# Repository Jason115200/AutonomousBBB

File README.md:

All code is severely outdated. The "REST Board" needs to be updated, but is proof of a great rough draft. For updated code and board, visit REST_Autonomous repository

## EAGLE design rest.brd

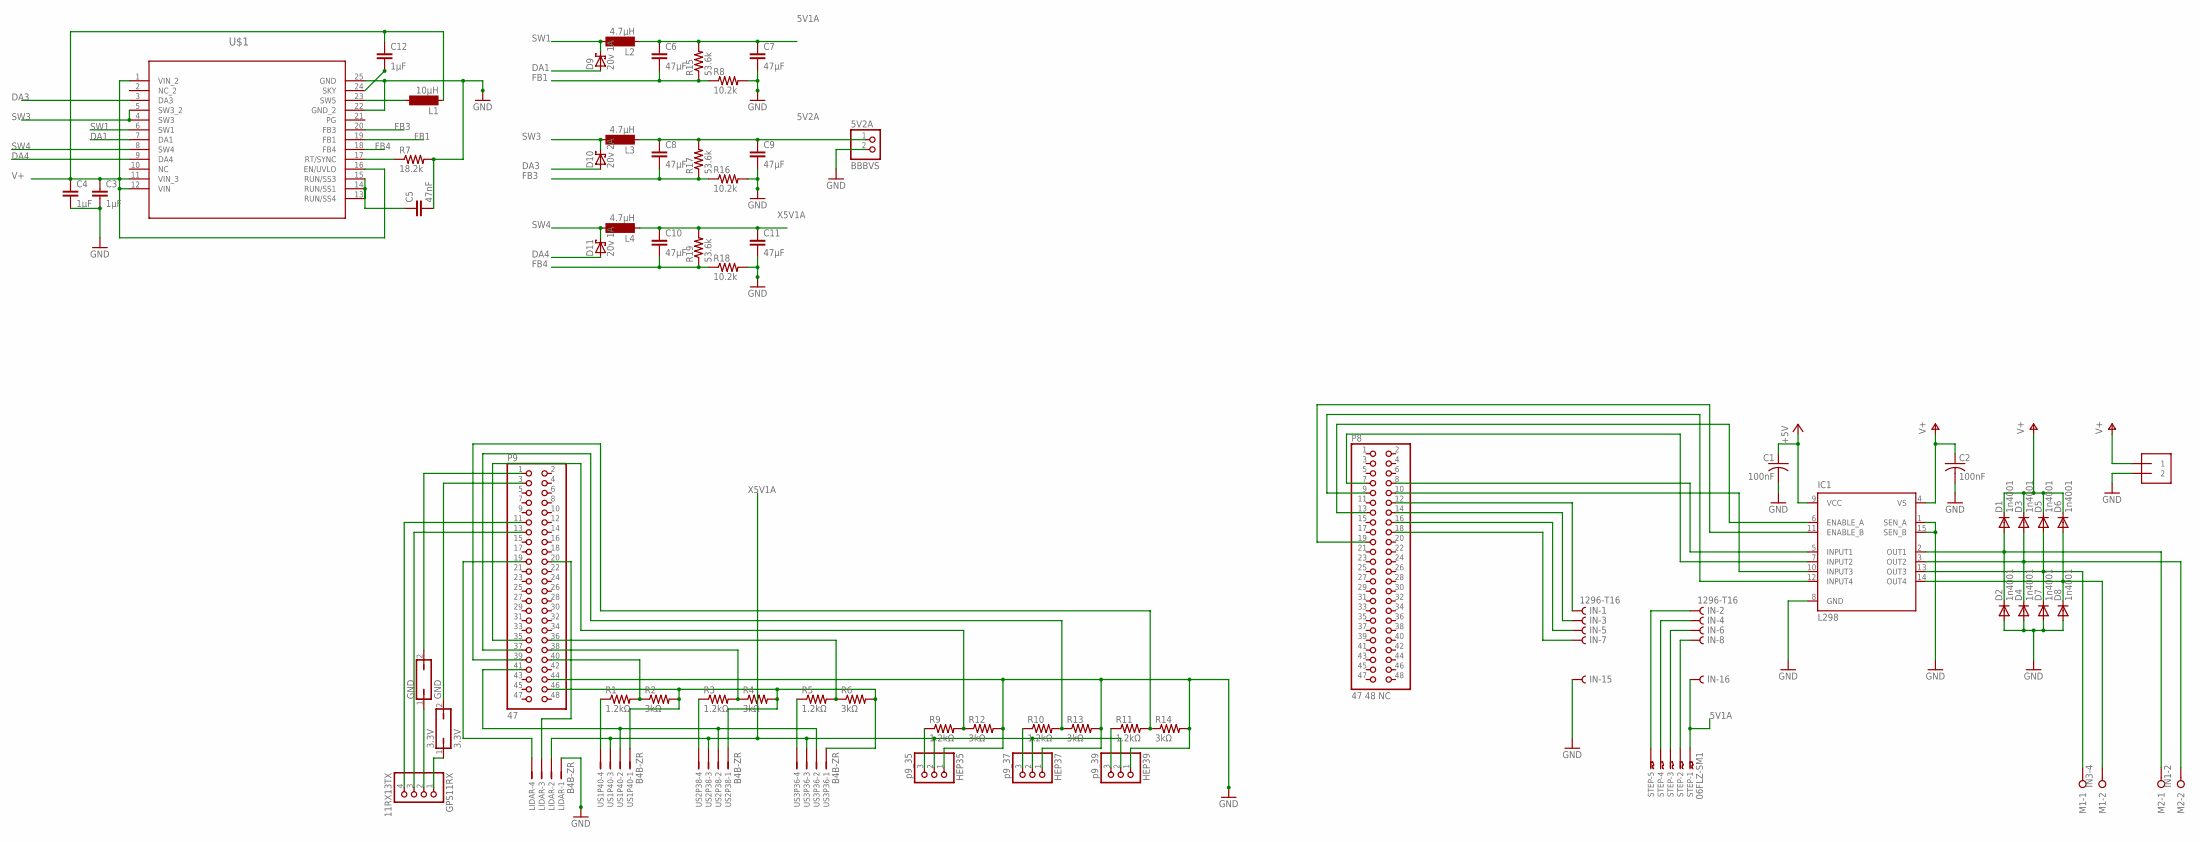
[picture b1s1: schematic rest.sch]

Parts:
3.3V: 3.3V; JP1
5V2A: BBBVS; 1X02
C1, C2: 100nF; C050-024X044
C3, C4, C12: 1µF; C2.5-3
C5: 47nF; C2.5-3
C6, C7, C8, C9, C10, C11: 47µF; C2.5-3
D1, D2, D3, D4, D5, D6, D7, D8: 1n4001; D-5
D9, D11: 20v 1A; DO41-7.6
D10: 20v 2A; DO41-7.6
GND: GND; JP1
GPS11RX: 11RX13TX; 1X04
HEP35: p9_35; JSTPH3
HEP37: p9_37; JSTPH3
HEP39: p9_39; JSTPH3
IC1: L298; MULTIWATT-15
IN: 1296-T16; 1296-18
J1: 1X2-3.5MM
L1: 10µH; SM-L15A
L2, L3, L4: 4.7µH; SM-L15A
LIDAR: B4B-ZR
M1: IN3-4; W237-132
M2: IN1-2; W237-132
P8: 47 48 NC; 2X24
P9: 47; 2X24
R1, R3, R5, R9, R10, R11: 1.2kΩ; 0309/12
R2, R4, R6, R12, R13, R14: 3kΩ; 0309/12
R7: 18.2k; 0204/5
R8, R16, R18: 10.2k; 0204/5
R15, R17, R19: 53.6k; 0204/5
STEP: 06FLZ-SM1; 6FLZ-SM
U$1: LT3514; TSSOP-24_FEAA
US1P40, US2P38, US3P36: B4B-ZR

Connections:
5V1A: C6.1, C7.1, IN.16, L2.1, R15.2, STEP.1
5V2A: 5V2A.1, C8.1, C9.1, L3.1, R17.2
+5V: C1.1, IC1.9 (VCC)
DA1: D9.A, U$1.7 (DA1)
DA3: D10.A, U$1.3 (DA3)
DA4: D11.A, U$1.9 (DA4)
FB1: C6.2, R8.1, R15.1, U$1.19 (FB1)
FB3: C8.2, R16.1, R17.1, U$1.20 (FB3)
FB4: C10.2, R18.1, R19.1, U$1.18 (FB4)
GND: 5V2A.2, C1.2, C2.2, C3.2, C4.2, C5.2, C7.2, C9.2, C11.2, D2.A, D4.A, D7.A, D8.A, HEP35.1, HEP37.1, HEP39.1, IC1.1 (SEN_A), IC1.8 (GND), IC1.15 (SEN_B), IN.15, J1.2, LIDAR.1, P9.44, R7.2, R8.2, R12.2, R13.2, R14.2, R16.2, R18.2, U$1.22 (GND_2), U$1.25 (GND)
unnamed: P9.40, R1.2, R2.1
unnamed: P9.38, R3.2, R4.1
unnamed: P9.36, R5.2, R6.1
unnamed: R1.1, US1P40.4
unnamed: R3.1, US2P38.4
unnamed: R5.1, US3P36.4
unnamed: P9.46, R2.2, R4.2, R6.2, US1P40.1, US2P38.1, US3P36.1
unnamed: P9.41, US1P40.2, US2P38.2, US3P36.2
unnamed: D1.A, D2.C, IC1.2 (OUT1), M2.1
unnamed: D3.A, D4.C, IC1.3 (OUT2), M2.2
unnamed: P9.39, R11.2, R14.1
unnamed: P9.37, R10.2, R13.1
unnamed: P9.35, R9.2, R12.1
unnamed: HEP35.3, R9.1
unnamed: HEP37.3, R10.1
unnamed: HEP39.3, R11.1
unnamed: D6.A, D8.C, IC1.14 (OUT4), M1.2
unnamed: D5.A, D7.C, IC1.13 (OUT3), M1.1
unnamed: IC1.5 (INPUT1), P8.8
unnamed: IC1.7 (INPUT2), P8.7
unnamed: IC1.6 (ENABLE_A), P8.13
unnamed: IC1.10 (INPUT3), P8.10
unnamed: IC1.12 (INPUT4), P8.9
unnamed: IC1.11 (ENABLE_B), P8.19
unnamed: IN.7, P8.18
unnamed: IN.3, P8.14
unnamed: IN.1, P8.12
unnamed: LIDAR.4, P9.19
unnamed: IN.5, P8.16
unnamed: IN.2, STEP.5
unnamed: IN.4, STEP.4
unnamed: IN.6, STEP.3
unnamed: IN.8, STEP.2
unnamed: LIDAR.3, P9.20
unnamed: GPS11RX.4, P9.11
unnamed: GPS11RX.3, P9.13
unnamed: GND.2, P9.1
unnamed: 3.3V.2, P9.3
unnamed: GND.1, GPS11RX.2
unnamed: 3.3V.1, GPS11RX.1
unnamed: C12.2, U$1.24 (SKY)
unnamed: L1.2, U$1.23 (SW5)
unnamed: C5.1, U$1.13 (RUN/SS4), U$1.14 (RUN/SS1), U$1.15 (RUN/SS3)
unnamed: R7.1, U$1.17 (RT/SYNC)
SW1: D9.C, L2.2, U$1.6 (SW1)
SW3: D10.C, L3.2, U$1.4 (SW3), U$1.5 (SW3_2)
SW4: D11.C, L4.2, U$1.8 (SW4)
V+: C2.1, C3.1, C4.1, C12.1, D1.C, D3.C, D5.C, D6.C, IC1.4 (VS), J1.1, L1.1, U$1.1 (VIN_2), U$1.11 (VIN_3), U$1.12 (VIN), U$1.16 (EN/UVLO)
X5V1A: C10.1, C11.1, HEP35.2, HEP37.2, HEP39.2, L4.1, LIDAR.2, R19.2, US1P40.3, US2P38.3, US3P36.3

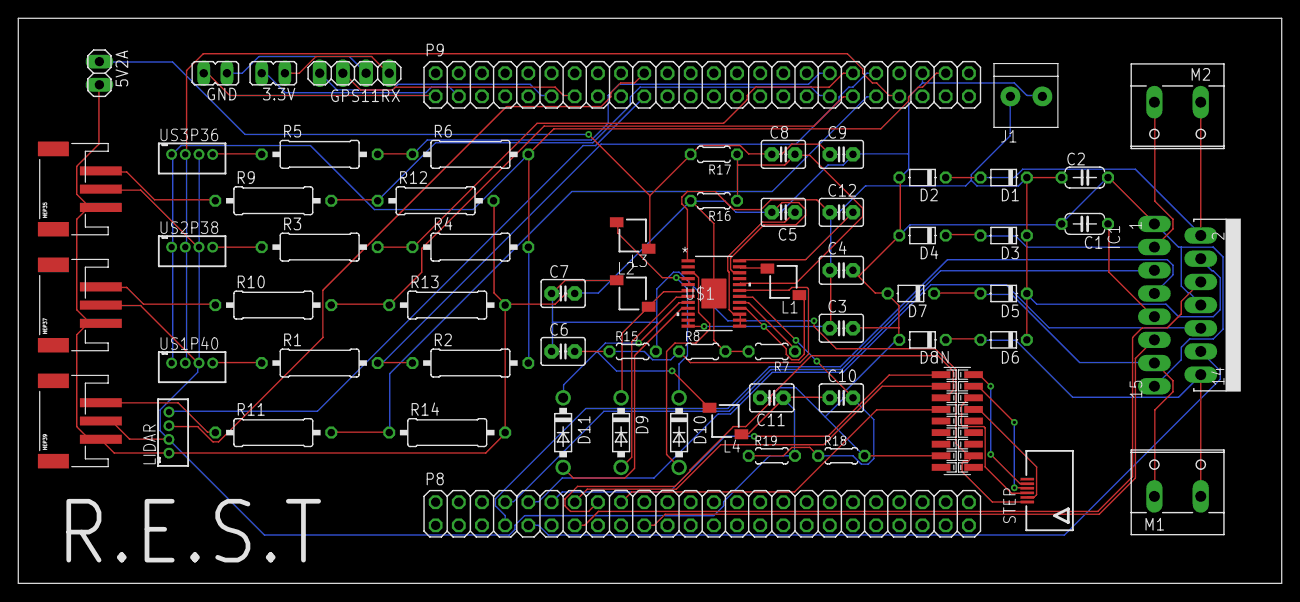
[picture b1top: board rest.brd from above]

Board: 2 copper layers, 138.4 x 61.9 mm, 66 parts (0 on the bottom side), 59 nets.
